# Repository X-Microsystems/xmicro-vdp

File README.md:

# XMICRO-VDP
Video card for the [XMICRO Bus](https://github.com/X-Microsystems/xmicro-bus), based on the Yamaha V9958 VDP

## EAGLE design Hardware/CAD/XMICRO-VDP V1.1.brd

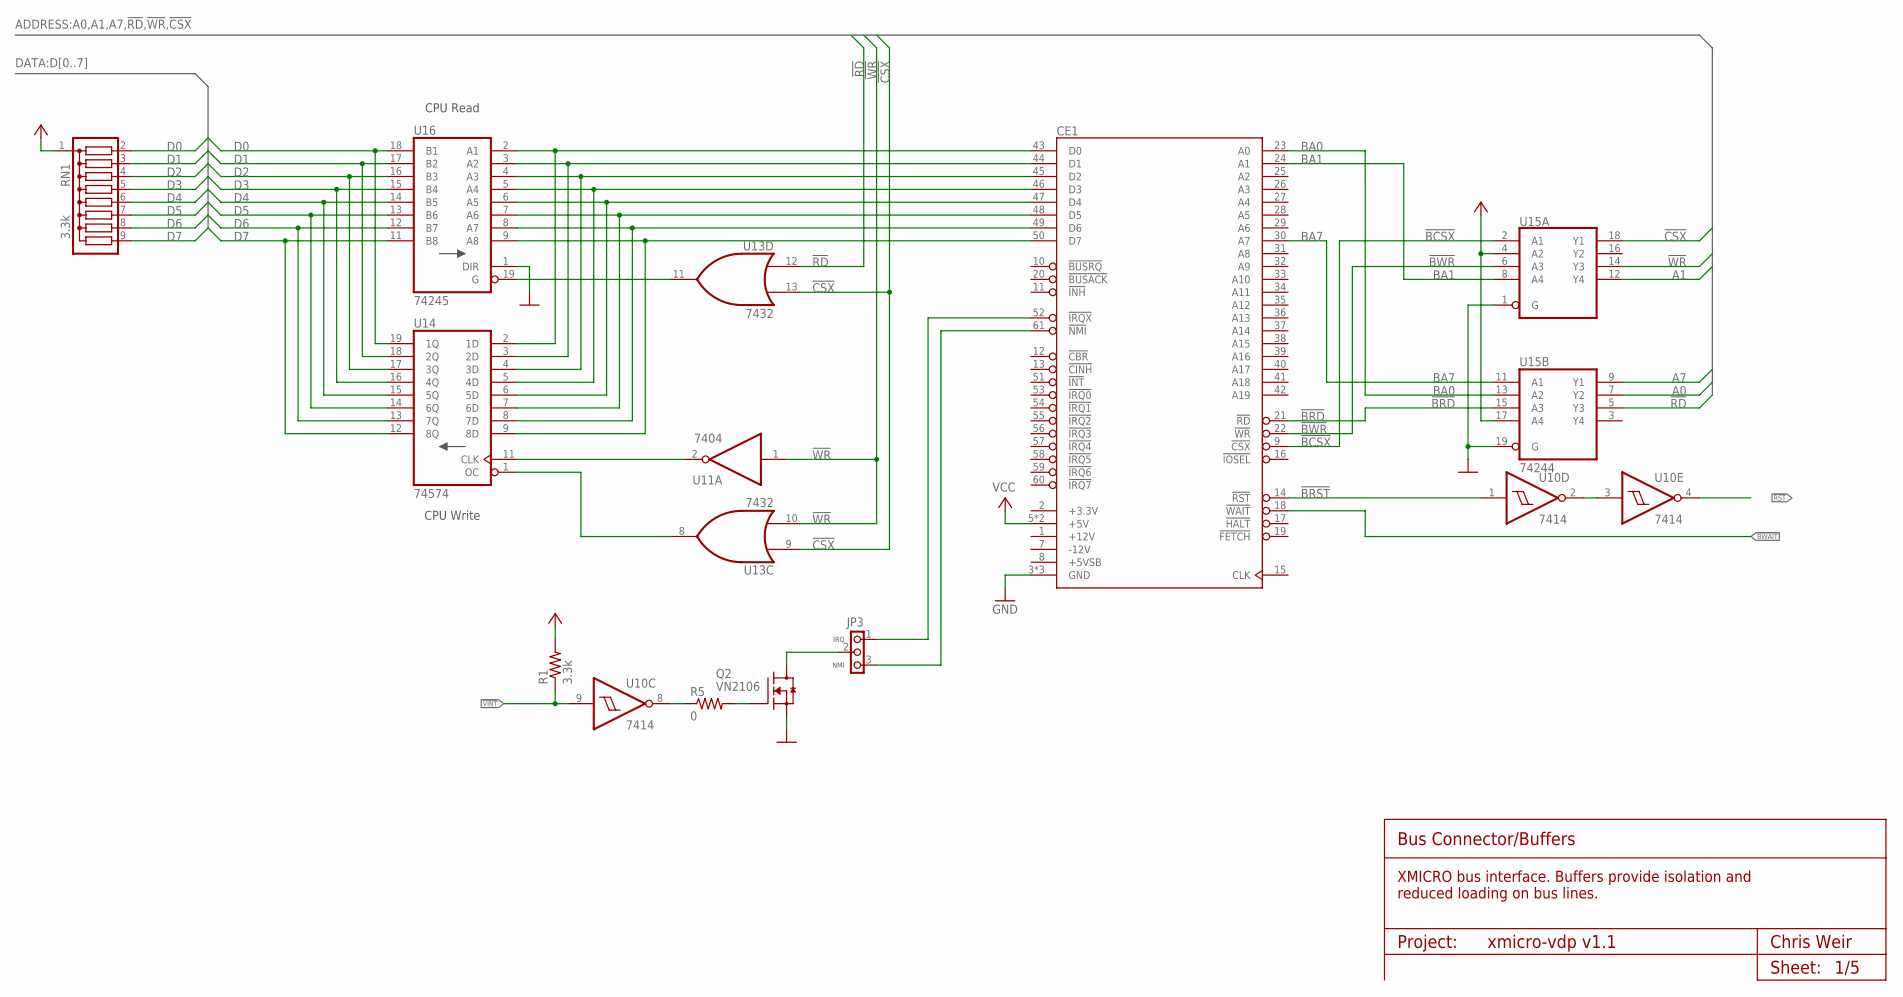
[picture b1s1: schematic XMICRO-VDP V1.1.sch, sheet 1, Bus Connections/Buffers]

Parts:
CE1: XMICRO-BUS-EDGE62M; EDGE62M
JP3: PINHD1X3THRU; 1X03
Q2: VN2106; TO92
R1: 3.3k; 0207/10
R5: 0; 0207/10
RN1: 3.3k; SIL9
U10: 7414; DIL14
U11: 7404; DIL14
U13: 7432; DIL14
U14: 74574; DIL20
U15: 74244; DIL20
U16: 74245; DIL20

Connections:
!BCSX: CE1.9 (!CSX), U15.2 (A1)
!BRD: CE1.21 (!RD), U15.15 (A3)
!BRST: CE1.14 (!RST), U10.1 (I)
!BWAIT: CE1.18 (!WAIT); also elsewhere on the board
!BWR: CE1.22 (!WR), U15.6 (A3)
!CSX: U13.9 (I0), U13.13 (I1), U15.18 (Y1); also elsewhere on the board
!RD: U13.12 (I0), U15.5 (Y3); also elsewhere on the board
!RST: U10.4 (O); also elsewhere on the board
!VINT: R1.1, U10.9 (I); also elsewhere on the board
!WR: U11.1 (I), U13.10 (I1), U15.14 (Y3); also elsewhere on the board
A0: U15.7 (Y2); also elsewhere on the board
A1: U15.12 (Y4); also elsewhere on the board
A7: U15.9 (Y1); also elsewhere on the board
BA0: CE1.23 (A0), U15.13 (A2)
BA1: CE1.24 (A1), U15.8 (A4)
BA7: CE1.30 (A7), U15.11 (A1)
D0: RN1.2, U14.19 (1Q), U16.18 (B1); also elsewhere on the board
D1: RN1.3, U14.18 (2Q), U16.17 (B2); also elsewhere on the board
D2: RN1.4, U14.17 (3Q), U16.16 (B3); also elsewhere on the board
D3: RN1.5, U14.16 (4Q), U16.15 (B4); also elsewhere on the board
D4: RN1.6, U14.15 (5Q), U16.14 (B5); also elsewhere on the board
D5: RN1.7, U14.14 (6Q), U16.13 (B6); also elsewhere on the board
D6: RN1.8, U14.13 (7Q), U16.12 (B7); also elsewhere on the board
D7: RN1.9, U14.12 (8Q), U16.11 (B8); also elsewhere on the board
GND: CE1.3 (GND), CE1.4 (GND), CE1.62 (GND), Q2.1 (S), U10.7 (GND), U11.7 (GND), U13.7 (GND), U14.10 (GND), U15.1 (G), U15.10 (GND), U15.19 (G), U16.1 (DIR), U16.10 (GND); also elsewhere on the board
unnamed: Q2.2 (G), R5.2
unnamed: JP3.2, Q2.3 (D)
unnamed: R5.1, U10.8 (O)
unnamed: U10.2 (O), U10.3 (I)
unnamed: CE1.50 (D7), U14.9 (8D), U16.9 (A8)
unnamed: CE1.49 (D6), U14.8 (7D), U16.8 (A7)
unnamed: CE1.48 (D5), U14.7 (6D), U16.7 (A6)
unnamed: CE1.47 (D4), U14.6 (5D), U16.6 (A5)
unnamed: CE1.46 (D3), U14.5 (4D), U16.5 (A4)
unnamed: CE1.45 (D2), U14.4 (3D), U16.4 (A3)
unnamed: CE1.44 (D1), U14.3 (2D), U16.3 (A2)
unnamed: CE1.43 (D0), U14.2 (1D), U16.2 (A1)
unnamed: U13.11 (O), U16.19 (G)
unnamed: U11.2 (O), U14.11 (CLK)
unnamed: U13.8 (O), U14.1 (OC)
unnamed: CE1.61 (!NMI), JP3.3
unnamed: CE1.52 (!IRQX), JP3.1
VCC: CE1.5 (+5V), CE1.6 (+5V), R1.2, RN1.1, U10.14 (VCC), U11.14 (VCC), U13.14 (VCC), U14.20 (VCC), U15.4 (A2), U15.17 (A4), U15.20 (VCC), U16.20 (VCC); also elsewhere on the board

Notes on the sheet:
CPU Read
CPU Write
IRQ
NMI
Project:
Chris Weir
Sheet:
Bus Connector/Buffers
XMICRO bus interface. Buffers provide isolation and reduced loading on bus lines.

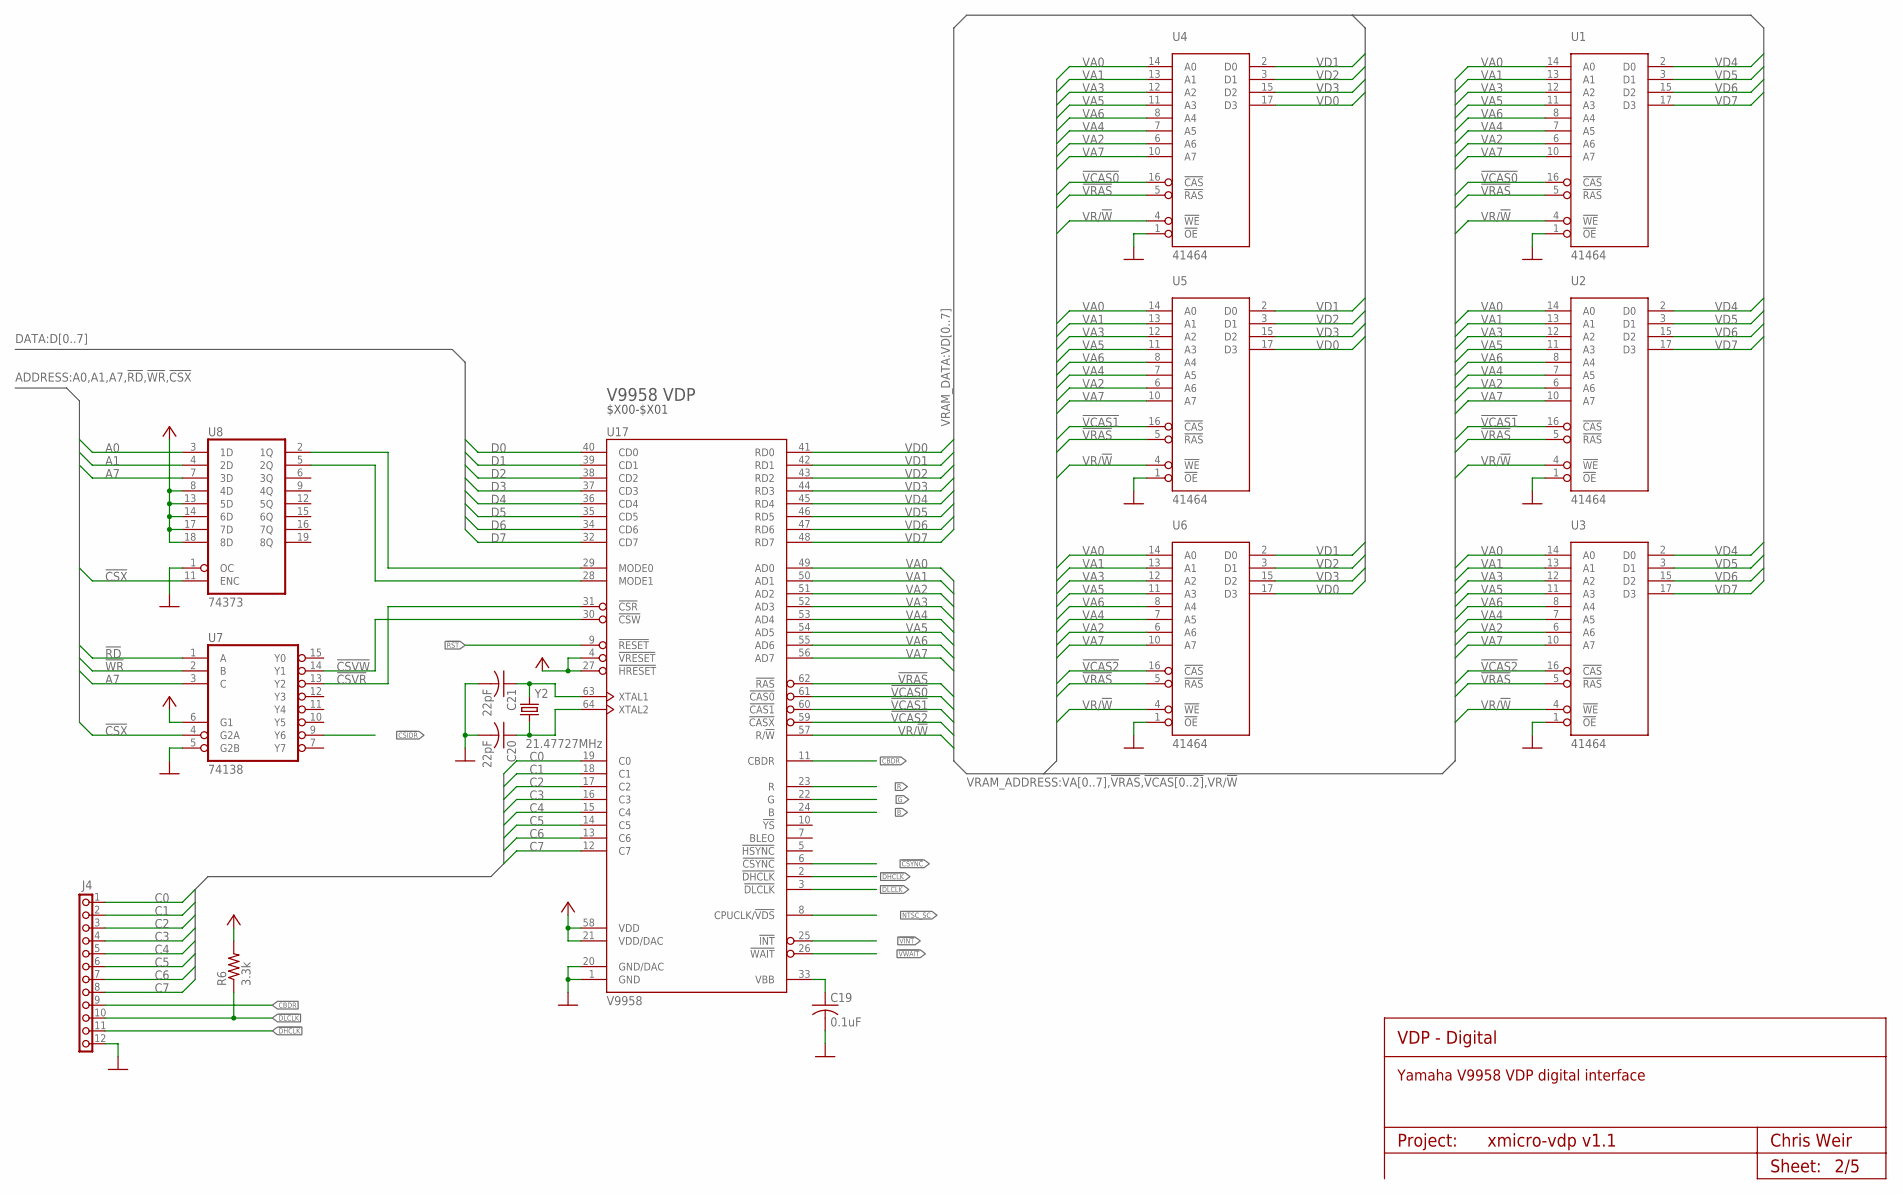
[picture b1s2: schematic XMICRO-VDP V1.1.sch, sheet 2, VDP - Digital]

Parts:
C19: 0.1uF; C100
C20, C21: 22pF; C100
J4: PINHD-2X6; 2X06
R6: 3.3k; 0207/10
U1, U2, U3, U4, U5, U6: 41464; DIL18
U7: 74138; DIL16
U8: 74373; DIL20
U17: V9958; SDIP64
Y2: 21.47727MHz; HC-49US

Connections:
!CSIDR: U7.9 (Y6); also elsewhere on the board
!CSVR: U7.13 (Y2), U17.31 (!CSR)
!CSVW: U7.14 (Y1), U17.30 (!CSW)
!CSX: U7.4 (G2A), U8.11 (ENC); also elsewhere on the board
!CSYNC: U17.6 (!CSYNC); also elsewhere on the board
!DHCLK: J4.11, U17.2 (!DHCLK)
!DLCLK: J4.10, R6.1, U17.3 (!DLCLK)
!RD: U7.1 (A); also elsewhere on the board
!RST: U17.9 (!RESET); also elsewhere on the board
!VCAS0: U1.16 (!CAS), U4.16 (!CAS), U17.61 (!CAS0)
!VCAS1: U2.16 (!CAS), U5.16 (!CAS), U17.60 (!CAS1)
!VCAS2: U3.16 (!CAS), U6.16 (!CAS), U17.59 (!CASX)
!VINT: U17.25 (!INT); also elsewhere on the board
!VRAS: U1.5 (!RAS), U2.5 (!RAS), U3.5 (!RAS), U4.5 (!RAS), U5.5 (!RAS), U6.5 (!RAS), U17.62 (!RAS)
!VWAIT: U17.26 (!WAIT); also elsewhere on the board
!WR: U7.2 (B); also elsewhere on the board
A0: U8.3 (1D); also elsewhere on the board
A1: U8.4 (2D); also elsewhere on the board
A7: U7.3 (C), U8.7 (3D); also elsewhere on the board
B: U17.24 (B); also elsewhere on the board
C0: J4.1, U17.19 (C0)
C1: J4.2, U17.18 (C1)
C2: J4.3, U17.17 (C2)
C3: J4.4, U17.16 (C3)
C4: J4.5, U17.15 (C4)
C5: J4.6, U17.14 (C5)
C6: J4.7, U17.13 (C6)
C7: J4.8, U17.12 (C7)
CBDR: J4.9, U17.11 (CBDR)
D0: U17.40 (CD0); also elsewhere on the board
D1: U17.39 (CD1); also elsewhere on the board
D2: U17.38 (CD2); also elsewhere on the board
D3: U17.37 (CD3); also elsewhere on the board
D4: U17.36 (CD4); also elsewhere on the board
D5: U17.35 (CD5); also elsewhere on the board
D6: U17.34 (CD6); also elsewhere on the board
D7: U17.32 (CD7); also elsewhere on the board
G: U17.22 (G); also elsewhere on the board
GND: C19.P$2 (2), C20.P$2 (2), C21.P$2 (2), J4.12, U1.1 (!OE), U1.18 (GND), U2.1 (!OE), U2.18 (GND), U3.1 (!OE), U3.18 (GND), U4.1 (!OE), U4.18 (GND), U5.1 (!OE), U5.18 (GND), U6.1 (!OE), U6.18 (GND), U7.5 (G2B), U7.8 (GND), U8.1 (OC), U8.10 (GND), U17.1 (GND), U17.20 (GND/DAC); also elsewhere on the board
unnamed: C21.P$1 (1), U17.63 (XTAL1), Y2.2
unnamed: C20.P$1 (1), U17.64 (XTAL2), Y2.1
unnamed: U8.2 (1Q), U17.29 (MODE0)
unnamed: C19.P$1 (1), U17.33 (VBB)
unnamed: U8.5 (2Q), U17.28 (MODE1)
NTSC_SC: U17.8 (CPUCLK/!VDS); also elsewhere on the board
R: U17.23 (R); also elsewhere on the board
VA0: U1.14 (A0), U2.14 (A0), U3.14 (A0), U4.14 (A0), U5.14 (A0), U6.14 (A0), U17.49 (AD0)
VA1: U1.13 (A1), U2.13 (A1), U3.13 (A1), U4.13 (A1), U5.13 (A1), U6.13 (A1), U17.50 (AD1)
VA2: U1.6 (A6), U2.6 (A6), U3.6 (A6), U4.6 (A6), U5.6 (A6), U6.6 (A6), U17.51 (AD2)
VA3: U1.12 (A2), U2.12 (A2), U3.12 (A2), U4.12 (A2), U5.12 (A2), U6.12 (A2), U17.52 (AD3)
VA4: U1.7 (A5), U2.7 (A5), U3.7 (A5), U4.7 (A5), U5.7 (A5), U6.7 (A5), U17.53 (AD4)
VA5: U1.11 (A3), U2.11 (A3), U3.11 (A3), U4.11 (A3), U5.11 (A3), U6.11 (A3), U17.54 (AD5)
VA6: U1.8 (A4), U2.8 (A4), U3.8 (A4), U4.8 (A4), U5.8 (A4), U6.8 (A4), U17.55 (AD6)
VA7: U1.10 (A7), U2.10 (A7), U3.10 (A7), U4.10 (A7), U5.10 (A7), U6.10 (A7), U17.56 (AD7)
VCC: R6.2, U1.9 (VCC), U2.9 (VCC), U3.9 (VCC), U4.9 (VCC), U5.9 (VCC), U6.9 (VCC), U7.6 (G1), U7.16 (VCC), U8.8 (4D), U8.13 (5D), U8.14 (6D), U8.17 (7D), U8.18 (8D), U8.20 (VCC), U17.4 (!VRESET), U17.21 (VDD/DAC), U17.27 (!HRESET), U17.58 (VDD); also elsewhere on the board
VD0: U4.17 (D3), U5.17 (D3), U6.17 (D3), U17.41 (RD0)
VD1: U4.2 (D0), U5.2 (D0), U6.2 (D0), U17.42 (RD1)
VD2: U4.3 (D1), U5.3 (D1), U6.3 (D1), U17.43 (RD2)
VD3: U4.15 (D2), U5.15 (D2), U6.15 (D2), U17.44 (RD3)
VD4: U1.2 (D0), U2.2 (D0), U3.2 (D0), U17.45 (RD4)
VD5: U1.3 (D1), U2.3 (D1), U3.3 (D1), U17.46 (RD5)
VD6: U1.15 (D2), U2.15 (D2), U3.15 (D2), U17.47 (RD6)
VD7: U1.17 (D3), U2.17 (D3), U3.17 (D3), U17.48 (RD7)
VR/!W: U1.4 (!WE), U2.4 (!WE), U3.4 (!WE), U4.4 (!WE), U5.4 (!WE), U6.4 (!WE), U17.57 (R/!W)

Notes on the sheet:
Project:
VDP - Digital
Chris Weir
Sheet:
Yamaha V9958 VDP digital interface
$X00-$X01
V9958 VDP

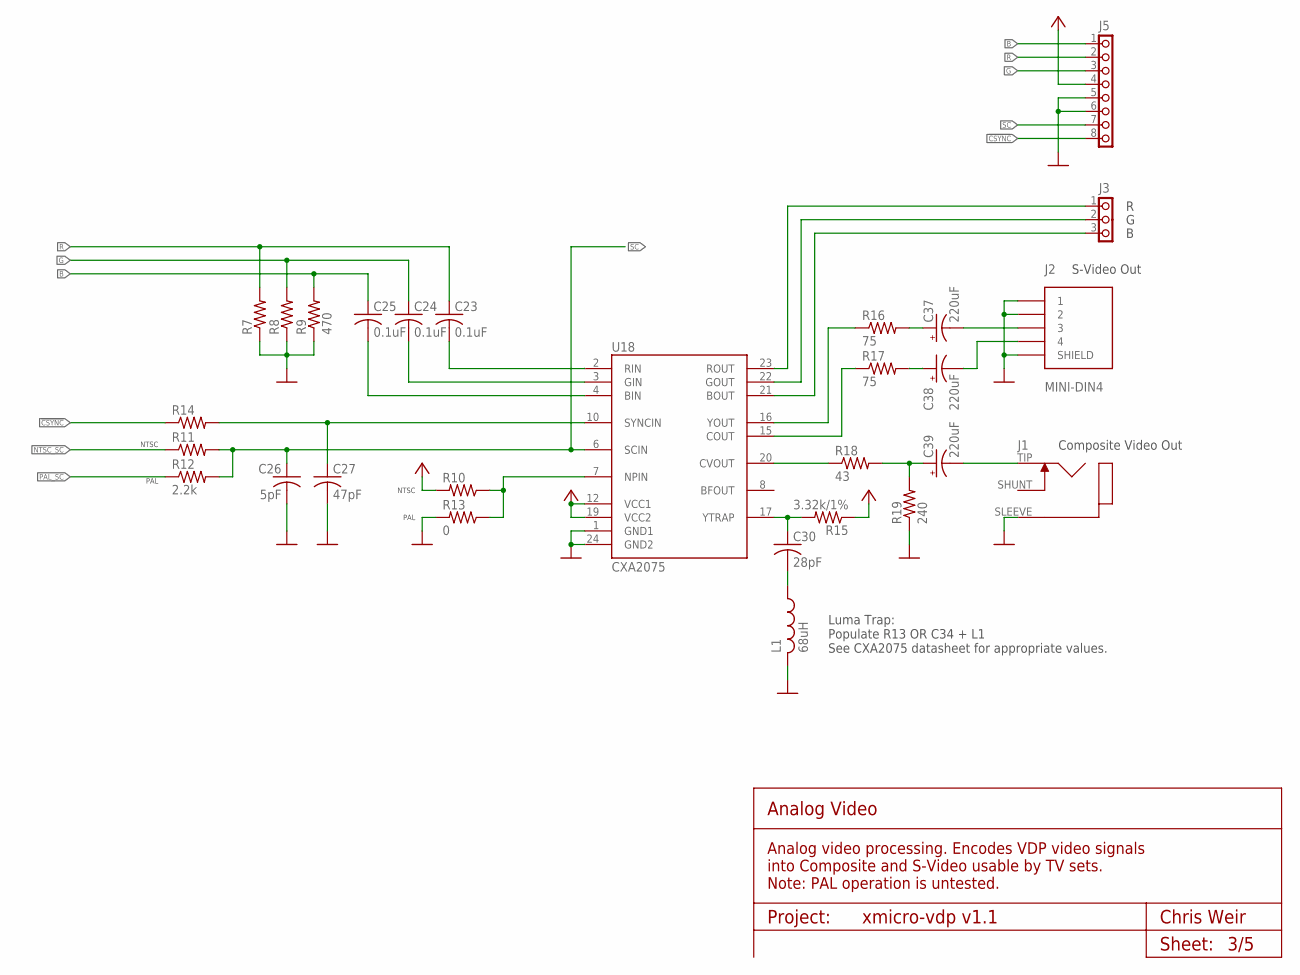
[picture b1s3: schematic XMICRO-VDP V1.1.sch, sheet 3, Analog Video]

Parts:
C23, C24, C25: 0.1uF; C100
C26: 5pF; C100
C27: 47pF; C100
C30: 28pF; C100
C37, C38, C39: 220uF; E2,5-7
J1: PJRAN1XU04AUX; PJRAN1
J2: MINI-DIN4
J3: PINHD1X3; 1X03
J5: PINHD-1X8; 1X08
L1: 68uH; 0207/10
R7, R8, R9: 470; 0207/10
R10, R13: 0; 0207/10
R11, R12, R14: 2.2k; 0207/10
R15: 3.32k/1%; 0207/10
R16, R17: 75; 0207/10
R18: 43; 0207/10
R19: 240; 0207/10
U18: CXA2075; SOP-24

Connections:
!CSYNC: J5.8, R14.1; also elsewhere on the board
B: C25.P$1 (1), J5.1, R9.2; also elsewhere on the board
G: C24.P$1 (1), J5.3, R8.2; also elsewhere on the board
GND: C26.P$2 (2), C27.P$2 (2), J1.SLEEVE, J2.1, J2.2, J2.G$1 (SHIELD), J2.G$2 (SHIELD), J2.G$3 (SHIELD), J5.5, J5.6, L1.2, R7.1, R8.1, R9.1, R13.2, R19.1, U18.1 (GND1), U18.24 (GND2); also elsewhere on the board
unnamed: J3.3, U18.21 (BOUT)
unnamed: C23.P$2 (2), U18.2 (RIN)
unnamed: C24.P$2 (2), U18.3 (GIN)
unnamed: C25.P$2 (2), U18.4 (BIN)
unnamed: J3.2, U18.22 (GOUT)
unnamed: J3.1, U18.23 (ROUT)
unnamed: R17.1, U18.15 (COUT)
unnamed: R16.1, U18.16 (YOUT)
unnamed: R18.1, U18.20 (CVOUT)
unnamed: C39.+, R18.2, R19.2
unnamed: C37.+, R16.2
unnamed: C38.+, R17.2
unnamed: C30.P$2 (2), L1.1
unnamed: C27.P$1 (1), R14.2, U18.10 (SYNCIN)
unnamed: R10.1, R13.1, U18.7 (NPIN)
unnamed: C38.-, J2.4
unnamed: C39.-, J1.TIP
unnamed: C30.P$1 (1), R15.2, U18.17 (YTRAP)
unnamed: C37.-, J2.3
NTSC_SC: R11.1; also elsewhere on the board
PAL_SC: R12.1; also elsewhere on the board
R: C23.P$1 (1), J5.2, R7.2; also elsewhere on the board
SC: C26.P$1 (1), J5.7, R11.2, R12.2, U18.6 (SCIN)
VCC: J5.4, R10.2, R15.1, U18.12 (VCC1), U18.19 (VCC2); also elsewhere on the board

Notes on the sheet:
NTSC
PAL
Composite Video Out
S-Video Out
Luma Trap: Populate R13 OR C34 + L1 See CXA2075 datasheet for appropriate values.
Project:
Analog Video
Chris Weir
Sheet:
Analog video processing. Encodes VDP video signals into Composite and S-Video usable by TV sets. Note: PAL operation is untested.

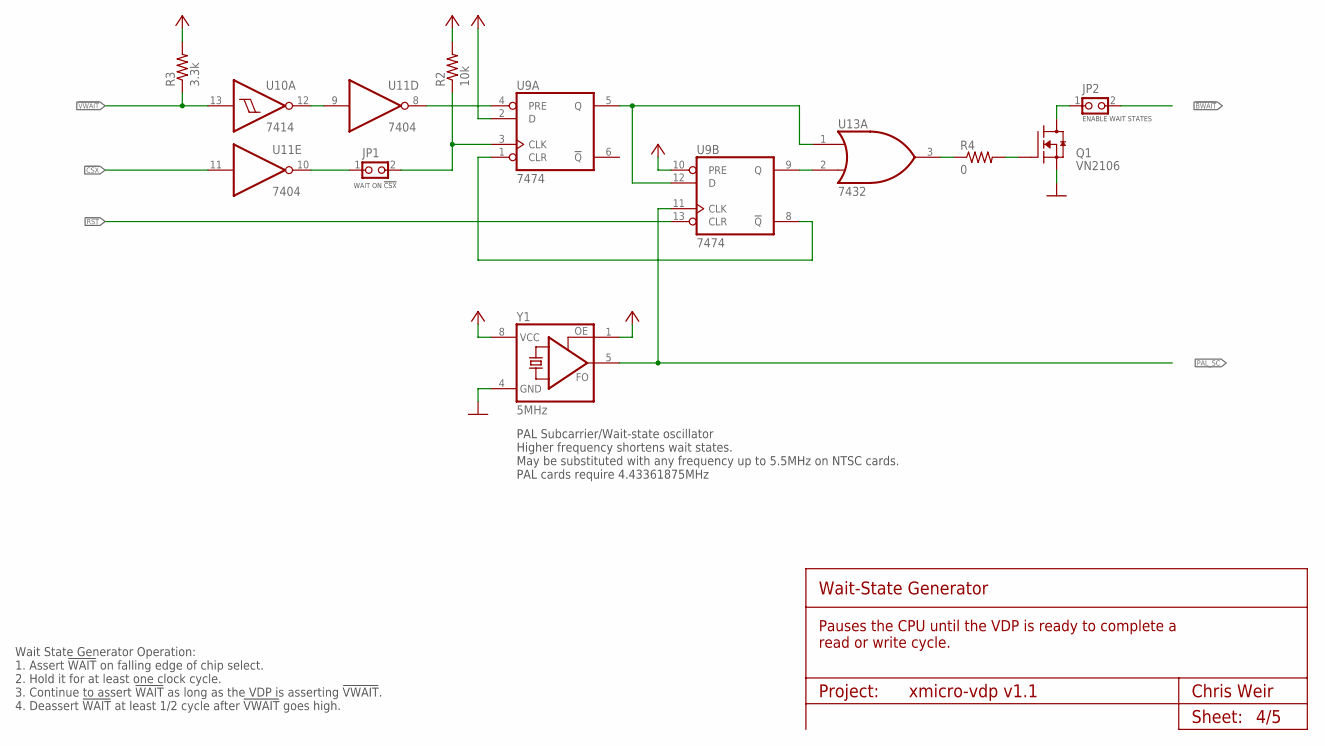
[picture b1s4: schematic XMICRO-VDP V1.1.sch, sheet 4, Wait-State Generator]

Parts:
JP1, JP2: PINHD-1X2THRU; 1X02
Q1: VN2106; TO92
R2: 10k; 0207/10
R3: 3.3k; 0207/10
R4: 0; 0207/10
U9: 7474; DIL14
U10: 7414; DIL14
U11: 7404; DIL14
U13: 7432; DIL14
Y1: 5MHz; DIL08S

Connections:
!BWAIT: JP2.2; also elsewhere on the board
!CSX: U11.11 (I); also elsewhere on the board
!RST: U9.13 (CLR); also elsewhere on the board
!VWAIT: R3.1, U10.13 (I); also elsewhere on the board
GND: Q1.1 (S), U9.7 (GND), U10.7 (GND), U11.7 (GND), U13.7 (GND), Y1.4 (GND); also elsewhere on the board
unnamed: U9.9 (Q), U13.2 (I1)
unnamed: JP2.1, Q1.3 (D)
unnamed: U9.4 (PRE), U11.8 (O)
unnamed: U10.12 (O), U11.9 (I)
unnamed: Q1.2 (G), R4.2
unnamed: JP1.1, U11.10 (O)
unnamed: R4.1, U13.3 (O)
unnamed: U9.5 (Q), U9.12 (D), U13.1 (I0)
unnamed: U9.1 (CLR), U9.8 (!Q)
unnamed: JP1.2, R2.1, U9.3 (CLK)
PAL_SC: U9.11 (CLK), Y1.5 (FO); also elsewhere on the board
VCC: R2.2, R3.2, U9.2 (D), U9.10 (PRE), U9.14 (VCC), U10.14 (VCC), U11.14 (VCC), U13.14 (VCC), Y1.1 (OE), Y1.8 (VCC); also elsewhere on the board

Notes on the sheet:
Wait State Generator Operation: 1. Assert !WAIT! on falling edge of chip select. 2. Hold it for at least one clock cycle. 3. Continue to assert !WAIT! as long as the VDP is asserting !VWAIT!. 4. Deassert !WAIT! at least 1/2 cycle after !VWAIT! goes high.
ENABLE WAIT STATES
WAIT ON !CSX!
PAL Subcarrier/Wait-state oscillator Higher frequency shortens wait states. May be substituted with any frequency up to 5.5MHz on NTSC cards. PAL cards require 4.43361875MHz
Project:
Wait-State Generator
Chris Weir
Sheet:
Pauses the CPU until the VDP is ready to complete a read or write cycle.

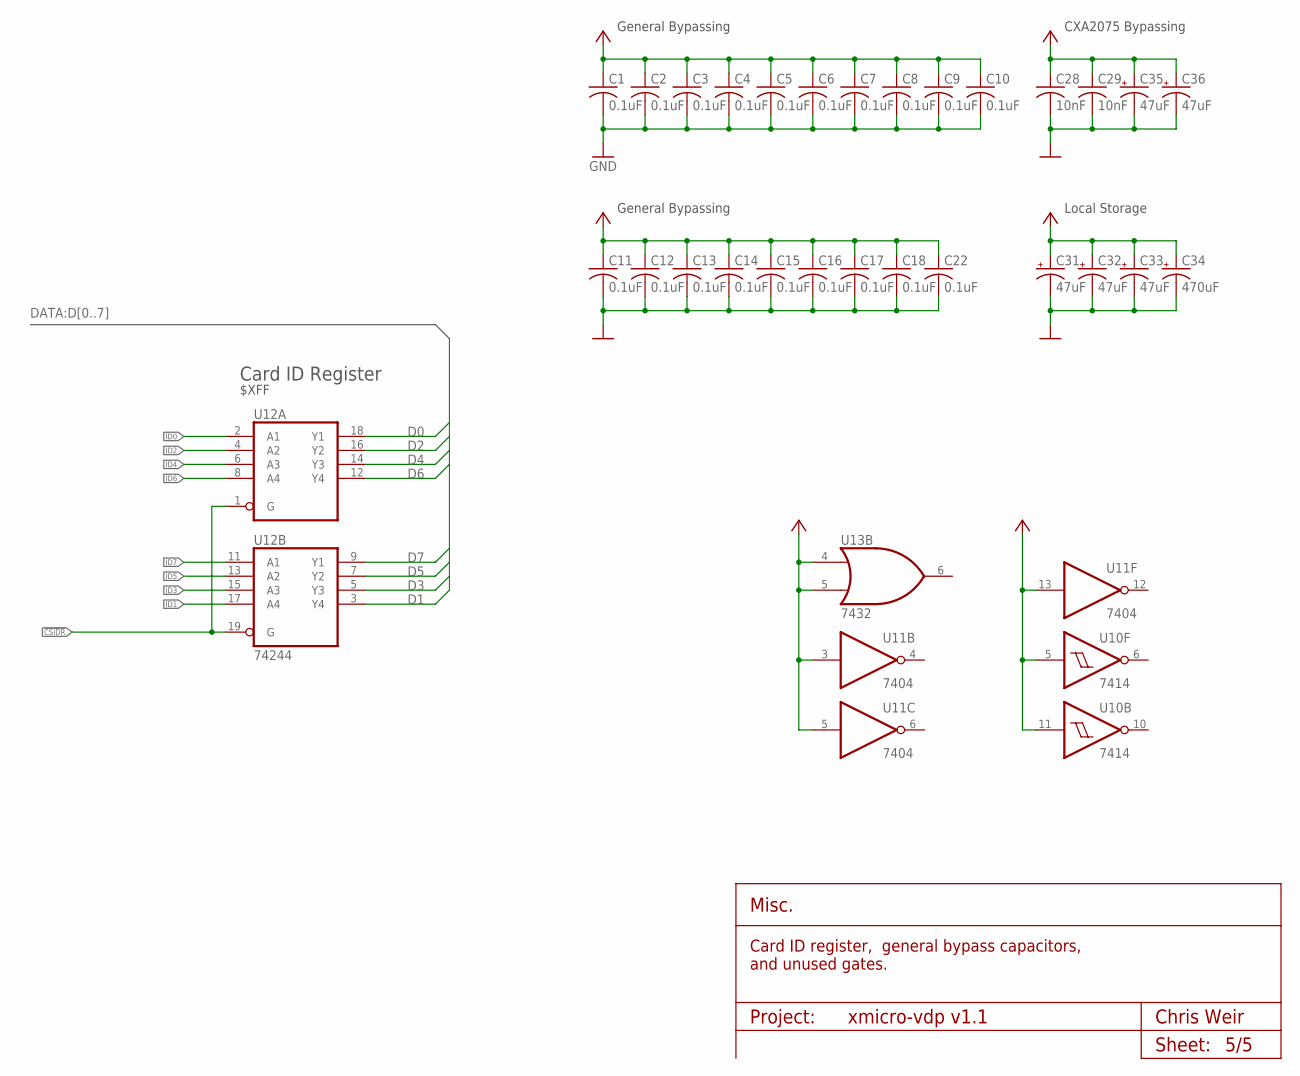
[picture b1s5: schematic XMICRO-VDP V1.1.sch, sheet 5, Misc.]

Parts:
C1, C2, C3, C4, C5, C6, C7, C8, C9, C10, C11, C12, C13, C14, C15, C16, C17, C18, C22: 0.1uF; C100
C28: 10nF; C100
C29: 10nF; C050-024X044
C31, C32, C33, C35, C36: 47uF; E2,5-6
C34: 470uF; C-10-5
U10: 7414; DIL14
U11: 7404; DIL14
U12: 74244; DIL20
U13: 7432; DIL14

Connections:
!CSIDR: U12.1 (G), U12.19 (G); also elsewhere on the board
D0: U12.18 (Y1); also elsewhere on the board
D1: U12.3 (Y4); also elsewhere on the board
D2: U12.16 (Y2); also elsewhere on the board
D3: U12.5 (Y3); also elsewhere on the board
D4: U12.14 (Y3); also elsewhere on the board
D5: U12.7 (Y2); also elsewhere on the board
D6: U12.12 (Y4); also elsewhere on the board
D7: U12.9 (Y1); also elsewhere on the board
GND: C1.P$2 (2), C2.P$2 (2), C3.P$2 (2), C4.P$2 (2), C5.P$2 (2), C6.P$2 (2), C7.P$2 (2), C8.P$2 (2), C9.P$2 (2), C10.P$2 (2), C11.P$2 (2), C12.P$2 (2), C13.P$2 (2), C14.P$2 (2), C15.P$2 (2), C16.P$2 (2), C17.P$2 (2), C18.P$2 (2), C22.P$2 (2), C28.P$2 (2), C29.2, C31.-, C32.-, C33.-, C34.-, C35.-, C36.-, U10.7 (GND), U11.7 (GND), U12.10 (GND), U13.7 (GND); also elsewhere on the board
ID0: U12.2 (A1)
ID1: U12.17 (A4)
ID2: U12.4 (A2)
ID3: U12.15 (A3)
ID4: U12.6 (A3)
ID5: U12.13 (A2)
ID6: U12.8 (A4)
ID7: U12.11 (A1)
VCC: C1.P$1 (1), C2.P$1 (1), C3.P$1 (1), C4.P$1 (1), C5.P$1 (1), C6.P$1 (1), C7.P$1 (1), C8.P$1 (1), C9.P$1 (1), C10.P$1 (1), C11.P$1 (1), C12.P$1 (1), C13.P$1 (1), C14.P$1 (1), C15.P$1 (1), C16.P$1 (1), C17.P$1 (1), C18.P$1 (1), C22.P$1 (1), C28.P$1 (1), C29.1, C31.+, C32.+, C33.+, C34.+, C35.+, C36.+, U10.5 (I), U10.11 (I), U10.14 (VCC), U11.3 (I), U11.5 (I), U11.13 (I), U11.14 (VCC), U12.20 (VCC), U13.4 (I0), U13.5 (I1), U13.14 (VCC); also elsewhere on the board

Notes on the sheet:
$XFF
Card ID Register
Project:
Misc.
Chris Weir
Sheet:
Card ID register, general bypass capacitors, and unused gates.
Local Storage
CXA2075 Bypassing
General Bypassing

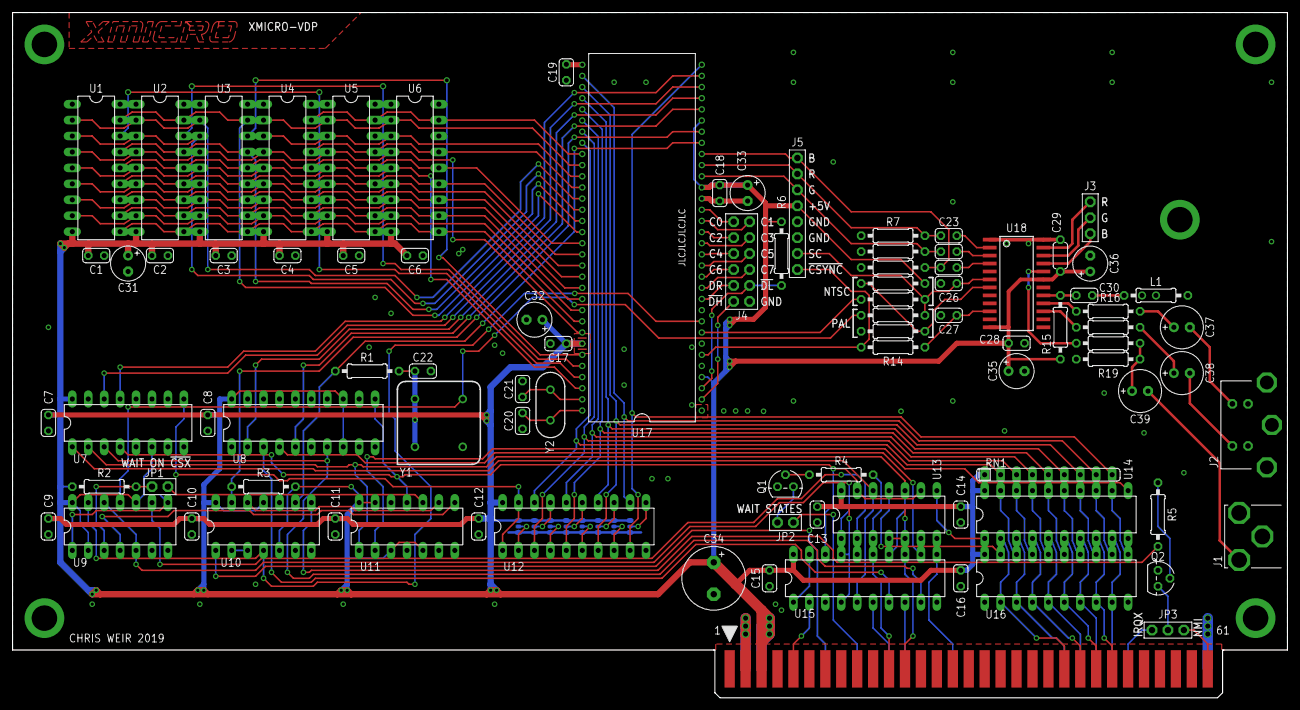
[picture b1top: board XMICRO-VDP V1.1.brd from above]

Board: 2 copper layers, 203.2 x 109.2 mm, 91 parts (0 on the bottom side), 120 nets.

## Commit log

2019-12-09 Updated to XMICRO-VDP V1.1. Replaced VRAM with dynamic RAM, various other minor tweaks.
2019-12-12 Updated manual.
2020-08-29 Updated manual
2020-08-29 Added pictures and updated README.md
